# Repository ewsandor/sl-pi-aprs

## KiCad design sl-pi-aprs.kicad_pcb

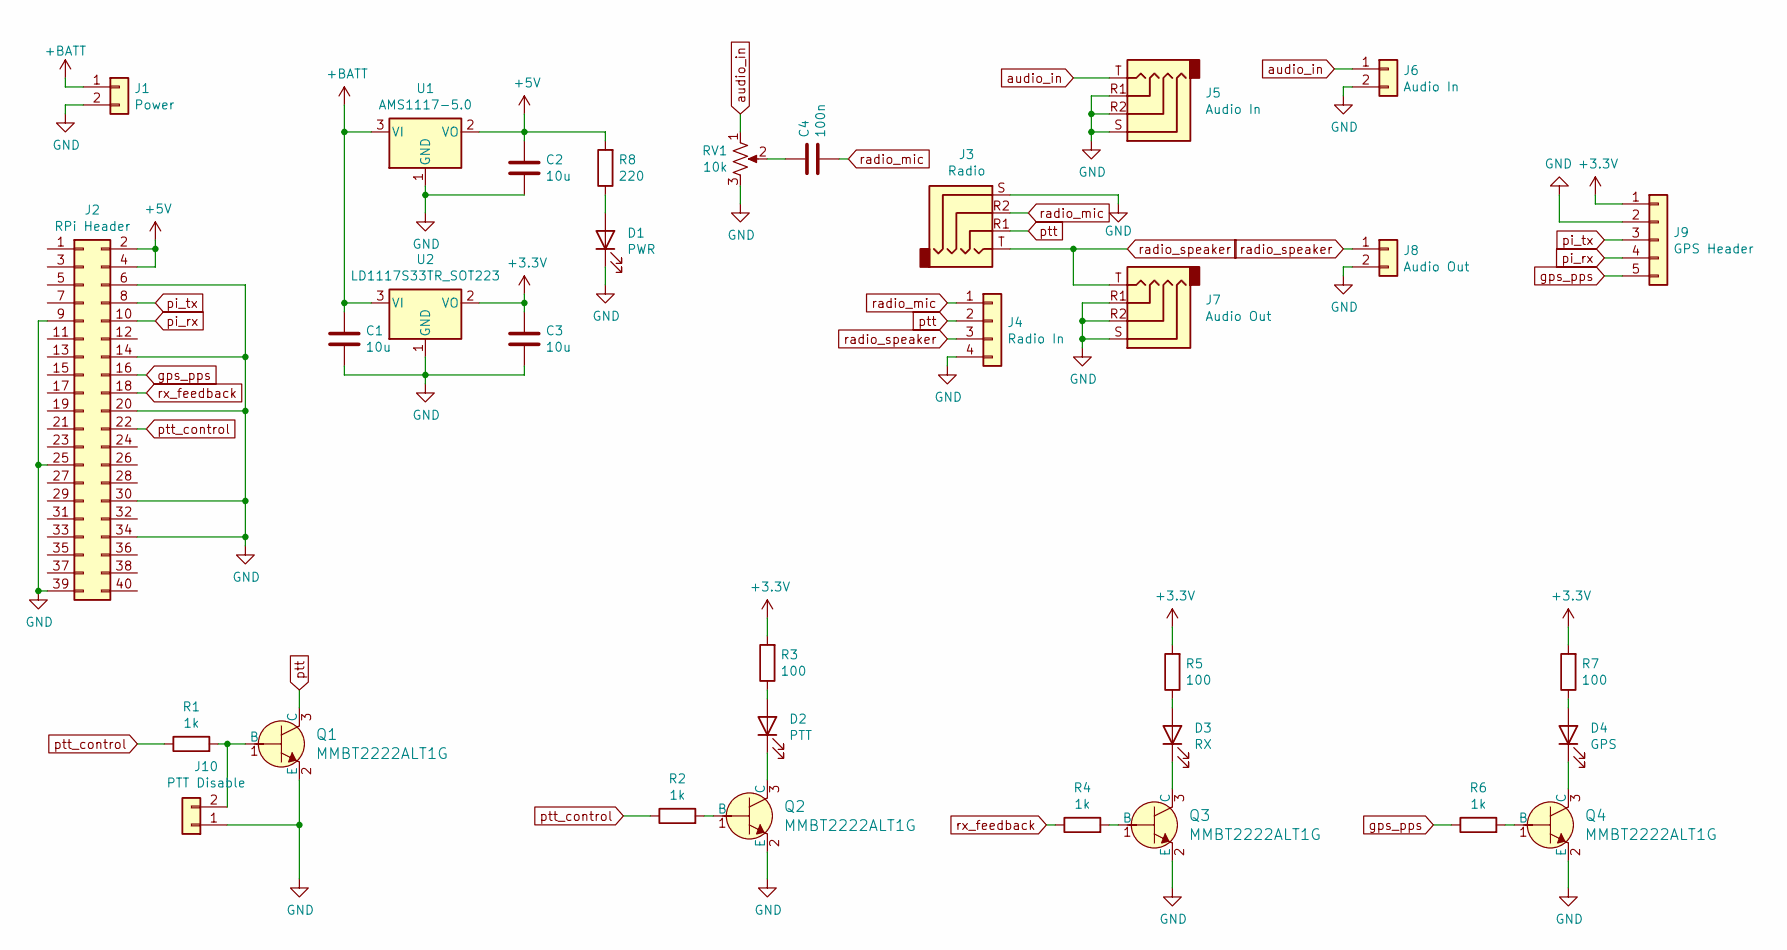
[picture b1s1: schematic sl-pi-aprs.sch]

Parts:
C1, C2, C3: 10u; C_0603_1608Metric_Pad1.08x0.95mm_HandSolder
C4: 100n; C_0603_1608Metric_Pad1.08x0.95mm_HandSolder
D1: PWR; LED_1206_3216Metric
D2: PTT; LED_1206_3216Metric
D3: RX; LED_1206_3216Metric
D4: GPS; LED_1206_3216Metric
J1: Power; PinHeader_1x02_P2.54mm_Vertical
J2: RPi Header; Raspberry_Pi_Zero_Socketed_THT_FaceDown_MountingHoles
J3: Radio; TRRS-PJ-320A_mod
J4: Radio In; PinHeader_1x04_P2.54mm_Vertical
J5: Audio In; TRRS-PJ-320A_mod
J6: Audio In; PinHeader_1x02_P2.54mm_Vertical
J7: Audio Out; TRRS-PJ-320A_mod
J8: Audio Out; PinHeader_1x02_P2.54mm_Vertical
J9: GPS Header; JST_XH_B5B-XH-A_1x05_P2.50mm_Vertical
J10: PTT Disable; PinHeader_1x02_P2.54mm_Vertical
Q1, Q2, Q3, Q4: MMBT2222ALT1G; SOT-23-3; MPN MMBT2222ALT1G; Digi-Key_PN MMBT2222ALT1GOSCT-ND
R1, R2, R4, R6: 1k; R_0603_1608Metric_Pad0.98x0.95mm_HandSolder
R3, R5, R7: 100; R_0603_1608Metric_Pad0.98x0.95mm_HandSolder
R8: 220; R_0603_1608Metric_Pad0.98x0.95mm_HandSolder
RV1: 10k; Potentiometer_Bourns_3296W_Vertical
U1: AMS1117-5.0; SOT-223-3_TabPin2
U2: LD1117S33TR_SOT223; SOT-223-3_TabPin2

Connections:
+3V3: C3.1, J9.1, R3.2, R5.2, R7.2, U2.2 (VO)
+5V: C2.1, J2.2, J2.4, R8.2, U1.2 (VO)
+BATT: C1.1, J1.1, U1.3 (VI), U2.3 (VI)
GND: C1.2, C2.2, C3.2, D1.1 (K), J1.2, J2.6, J2.9, J2.14, J2.20, J2.25, J2.30, J2.34, J2.39, J3.S, J4.4, J5.R1, J5.R2, J5.S, J6.2, J7.R1, J7.R2, J7.S, J8.2, J9.2, J10.1, Q1.2 (E), Q2.2 (E), Q3.2 (E), Q4.2 (E), RV1.3, U1.1 (GND), U2.1 (GND)
unnamed: C4.1, RV1.2
unnamed: D1.2 (A), R8.1
unnamed: D2.1 (K), Q2.3 (C)
unnamed: D2.2 (A), R3.1
unnamed: D3.1 (K), Q3.3 (C)
unnamed: D3.2 (A), R5.1
unnamed: D4.1 (K), Q4.3 (C)
unnamed: D4.2 (A), R7.1
unnamed: J10.2, Q1.1 (B), R1.2
unnamed: Q2.1 (B), R2.2
unnamed: Q3.1 (B), R4.2
unnamed: Q4.1 (B), R6.2
audio_in: J5.T, J6.1, RV1.1
gps_pps: J2.16, J9.5, R6.1
pi_rx: J2.10, J9.4
pi_tx: J2.8, J9.3
ptt: J3.R1, J4.2, Q1.3 (C)
ptt_control: J2.22, R1.1, R2.1
radio_mic: C4.2, J3.R2, J4.1
radio_speaker: J3.T, J4.3, J7.T, J8.1
rx_feedback: J2.18, R4.1

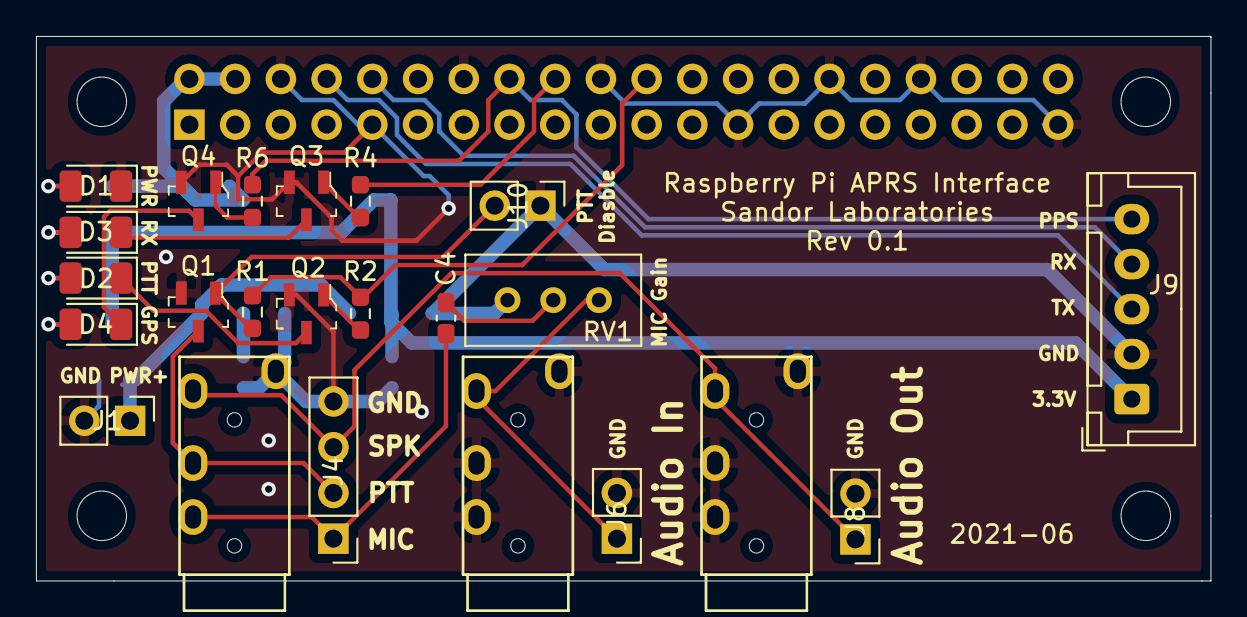
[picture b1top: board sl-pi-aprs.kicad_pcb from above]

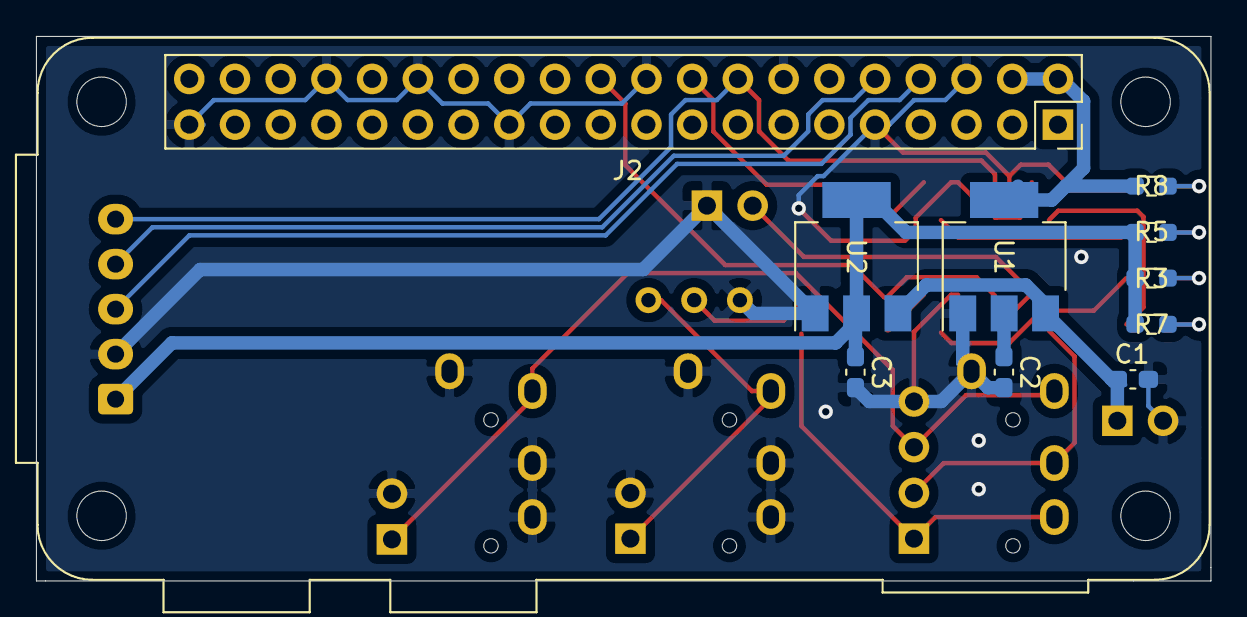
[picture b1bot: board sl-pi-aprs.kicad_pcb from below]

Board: 2 copper layers, 65.2 x 30.2 mm, 33 parts (10 on the bottom side), 25 nets.

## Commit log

2021-06-10 Initial commit as is
2021-06-10 reorder LEDs. Labelling
2021-06-10 Add ground planes and minor adjustments
2021-06-10 Final tweaks for REV 0.1
2021-06-10 Revision 0.1
